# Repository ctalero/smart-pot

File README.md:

# smart-pot
The files needed for the project to work are the "ssd1306.py" which is the library that controls the oled screen, and the "main.py" file which has all the principal functions of the whole circuit.

The typical problems one might experience while running the code is:
1°- The Dht11 module is not connected properly.
2°- The Oled Screen is not connected properly.
3°- The ssid and the password weren't being declared properly.

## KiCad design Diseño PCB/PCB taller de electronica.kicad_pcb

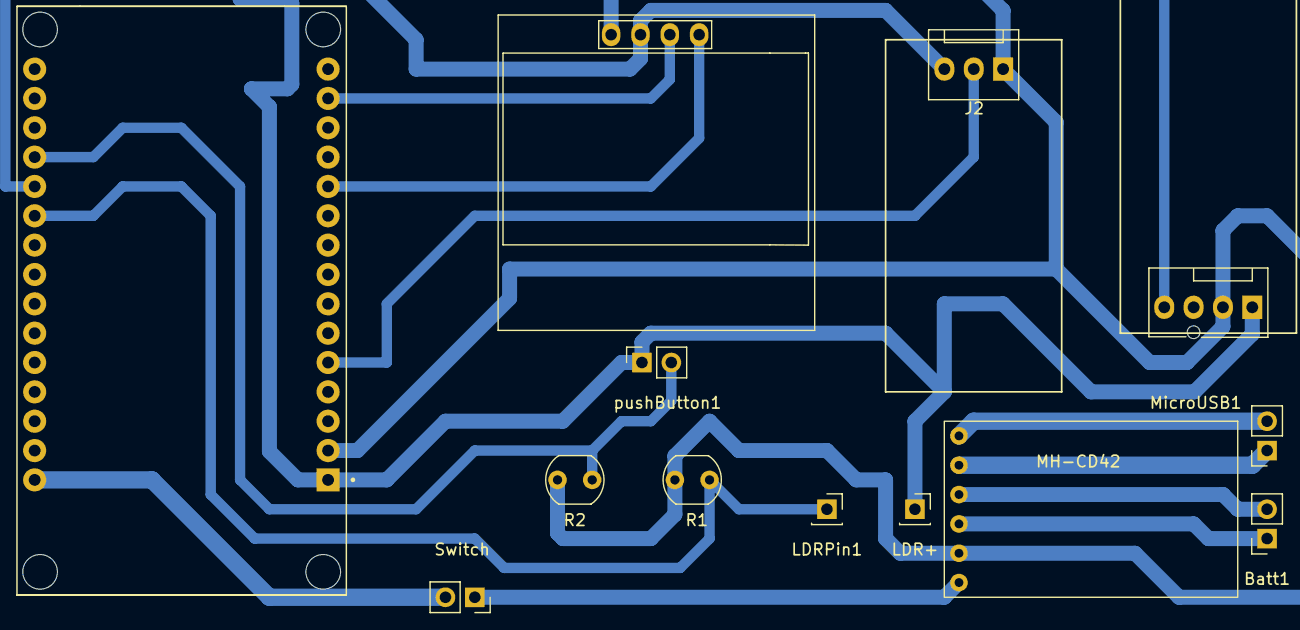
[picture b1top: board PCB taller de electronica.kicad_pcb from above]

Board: 2 copper layers, 13 parts (0 on the bottom side), 13 nets.

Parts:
Batt1: Conn_01x02_Socket; PinSocket_1x02_P2.54mm_Vertical
Brd1: SSD1306; 128x64OLED
J1: Conn_01x04_Socket; FanPinHeader_1x04_P2.54mm_Vertical
J2: DHT11; FanPinHeader_1x03_P2.54mm_Vertical
LDR+: Conn_01x01_Socket; PinSocket_1x01_P2.54mm_Vertical
LDRPin1: Conn_01x01_Socket; PinSocket_1x01_P2.54mm_Vertical
MicroUSB1: Conn_01x02_Socket; PinSocket_1x02_P2.54mm_Vertical
R1, R2: R; R_LDR_5.0x4.1mm_P3mm_Vertical
Switch: Conn_01x02_Socket; PinSocket_1x02_P2.54mm_Vertical
U1: ESP32; MODULE_ESP32_DEVKIT_V1
U2: MH-CD42; mh-cd42
pushButton1: Conn_01x02_Socket; PinSocket_1x02_P2.54mm_Vertical

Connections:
+3.3V: Brd1.2 (VCC), J1.1, J2.3, LDR+.1, U1.1 (3V3), pushButton1.1
+5V: Switch.1, U2.6 (OUT-5V)
+BATT: Batt1.1, U2.4 (BAT)
/d4: J2.2, U1.5 (D4)
/scl: Brd1.3 (SCL), U1.14 (D22)
/sda: Brd1.4 (SDA), U1.11 (D21)
GND: Batt1.2, Brd1.1 (GND), J1.2, J2.1, R1.1, R2.2, U1.2 (GND), U1.29 (GND), U2.3 (GND), U2.5 (GND)
unnamed: J1.4, U1.20 (D35)
unnamed: LDRPin1.1, R1.2, U1.21 (D32)
unnamed: MicroUSB1.1, U2.2 (GND)
unnamed: MicroUSB1.2, U2.1 (VIN)
unnamed: R2.1, U1.19 (D34), pushButton1.2
unnamed: Switch.2, U1.30 (VIN)

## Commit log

2023-11-04 Pending changes exported from your codespace
